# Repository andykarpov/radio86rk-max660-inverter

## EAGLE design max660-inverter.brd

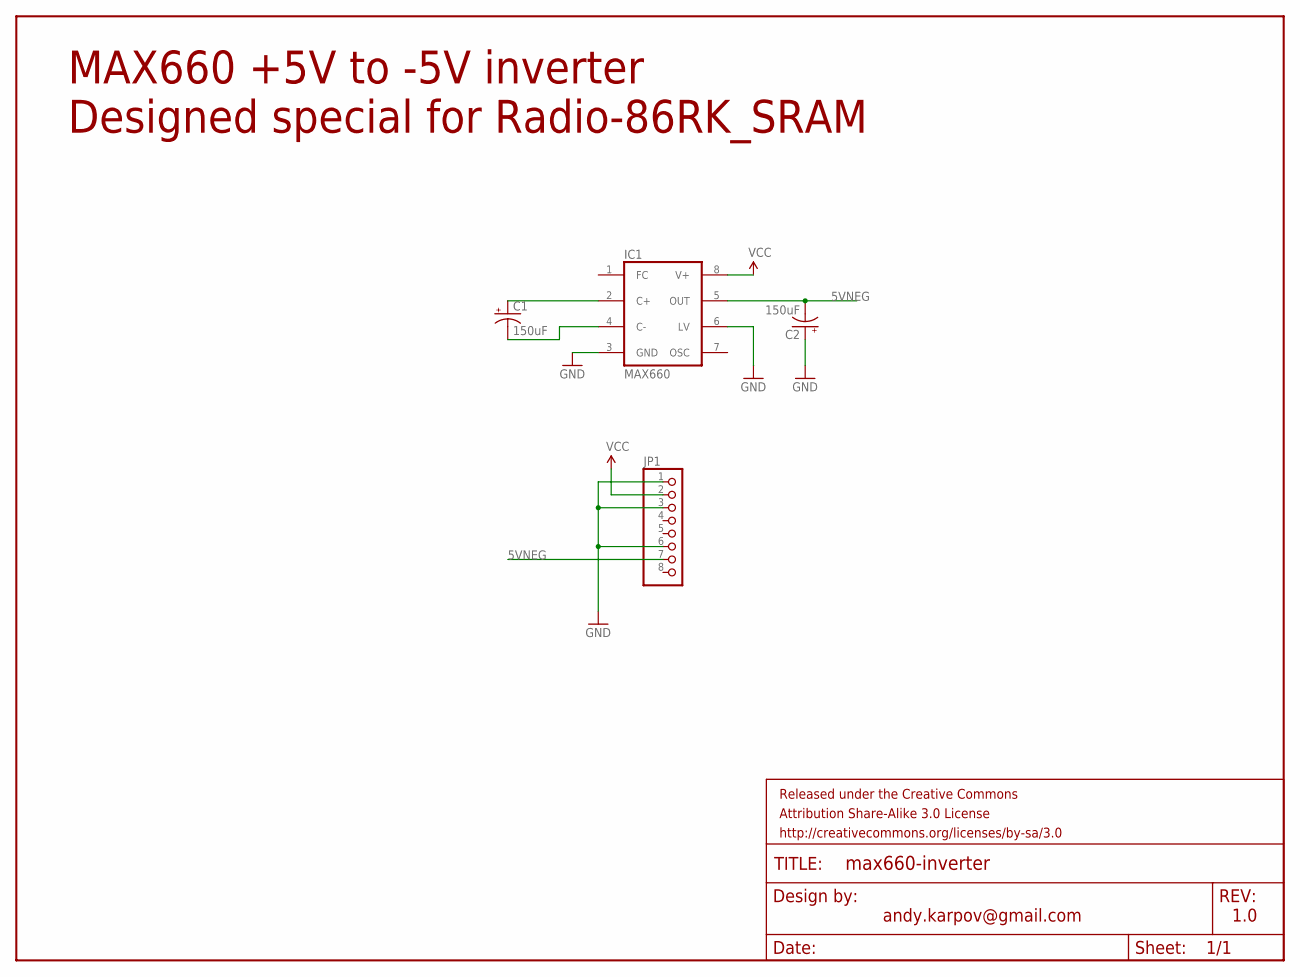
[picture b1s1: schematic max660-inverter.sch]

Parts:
C1, C2: 150uF; PANASONIC_D
FRAME1: FRAME-LETTER; CREATIVE_COMMONS
IC1: MAX660; SO08
JP1: PINHD-1X8; 1X08

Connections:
5VNEG: C2.-, IC1.5 (OUT), JP1.7
GND: C2.+, IC1.3 (GND), IC1.6 (LV), JP1.1, JP1.3, JP1.6
unnamed: C1.-, IC1.4 (C-)
unnamed: C1.+, IC1.2 (C+)
VCC: IC1.8 (V+), JP1.2

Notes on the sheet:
andy.karpov@gmail.com
1.0
MAX660 +5V to -5V inverter Designed special for Radio-86RK_SRAM

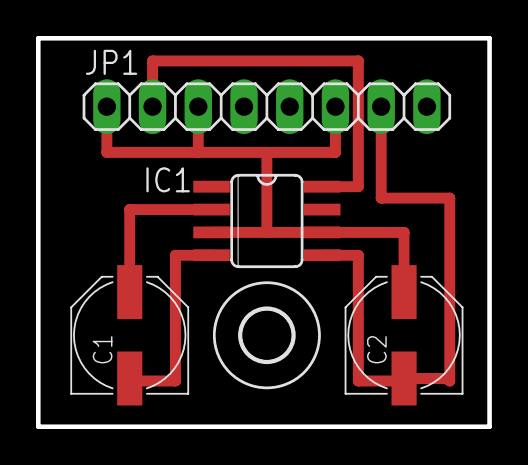
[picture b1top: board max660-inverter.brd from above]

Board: 2 copper layers, 25.1 x 21.6 mm, 6 parts (0 on the bottom side), 5 nets.

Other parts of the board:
U$1: 2,8

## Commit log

2016-04-08 initial version

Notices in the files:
parts and their libraries:
SparkFun-Capacitors: Licensing: CC v3.0 Share-Alike You are welcome to use this library for commercial purposes.
SparkFun-Aesthetics: Released under the Creative Commons Attribution Share-Alike 3.0 License
SparkFun-Aesthetics: http://creativecommons.org/licenses/by-sa/3.0
